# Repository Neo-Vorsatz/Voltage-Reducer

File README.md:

# Voltage Reducer
This repository includes the design files (KiCAD 9.0) and datasheet for a simple circuit that reduces DC voltages.
The datasheet has more information.

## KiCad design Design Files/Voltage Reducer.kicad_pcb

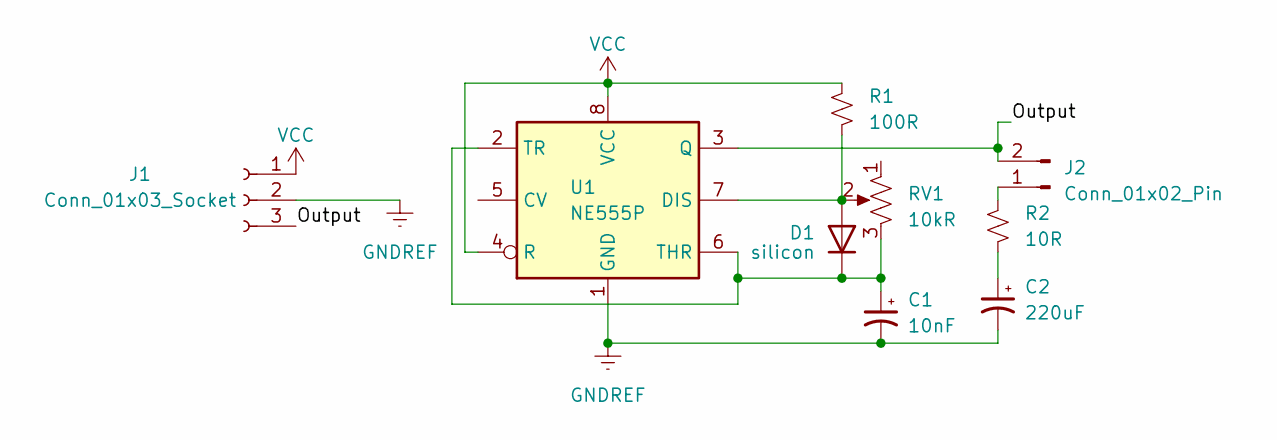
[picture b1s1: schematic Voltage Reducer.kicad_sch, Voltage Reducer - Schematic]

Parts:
C1: 10nF; R_Axial_DIN0204_L3.6mm_D1.6mm_P1.90mm_Vertical
C2: 220uF; CP_Radial_Tantal_D6.0mm_P2.50mm
D1: silicon; D_DO-41_SOD81_P2.54mm_Vertical_AnodeUp
J1: Conn_01x03_Socket; PinHeader_1x03_P2.54mm_Vertical
J2: Conn_01x02_Pin; PinHeader_1x02_P2.54mm_Vertical
R1: 100R; R_Axial_DIN0207_L6.3mm_D2.5mm_P2.54mm_Vertical
R2: 10R; R_Axial_DIN0207_L6.3mm_D2.5mm_P2.54mm_Vertical
RV1: 10kR; Potentiometer_Vishay_T73YP_Vertical
U1: NE555P; DIP-8_W7.62mm_Socket

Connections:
/Output: J1.3, J2.2, U1.3 (Q)
GNDREF: C1.2, C2.2, J1.2, U1.1 (GND)
unnamed: C2.1, R2.2
unnamed: D1.2 (A), R1.2, RV1.2, U1.7 (DIS)
unnamed: C1.1, D1.1 (K), RV1.3, U1.2 (TR), U1.6 (THR)
unnamed: J2.1, R2.1
VCC: J1.1, R1.1, U1.4 (R), U1.8 (VCC)

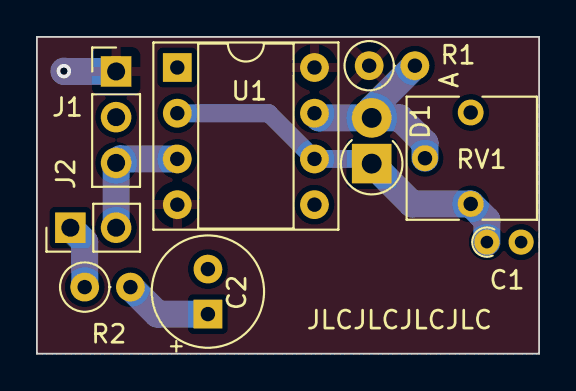
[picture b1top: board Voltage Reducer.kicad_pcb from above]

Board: 2 copper layers, 27.9 x 17.6 mm, 9 parts (0 on the bottom side), 7 nets.
